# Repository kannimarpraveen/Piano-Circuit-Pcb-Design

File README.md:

# Piano Circuit PCB Design

## Description
Designed a piano circuit PCB using EAGLE, converting a schematic into a fully routed PCB layout ready for fabrication.

## Features
- Multi-key input circuit design
- Compact PCB layout with optimized routing
- Proper component placement and trace design
- Gerber file generation for manufacturing

## Tools Used
- Autodesk EAGLE

## Files Included
- Schematic design
- PCB layout

## Working
The circuit generates different tones based on key inputs, simulating a basic electronic piano functionality.

## Outcome
Developed practical experience in PCB design workflow from schematic creation to fabrication-ready output.

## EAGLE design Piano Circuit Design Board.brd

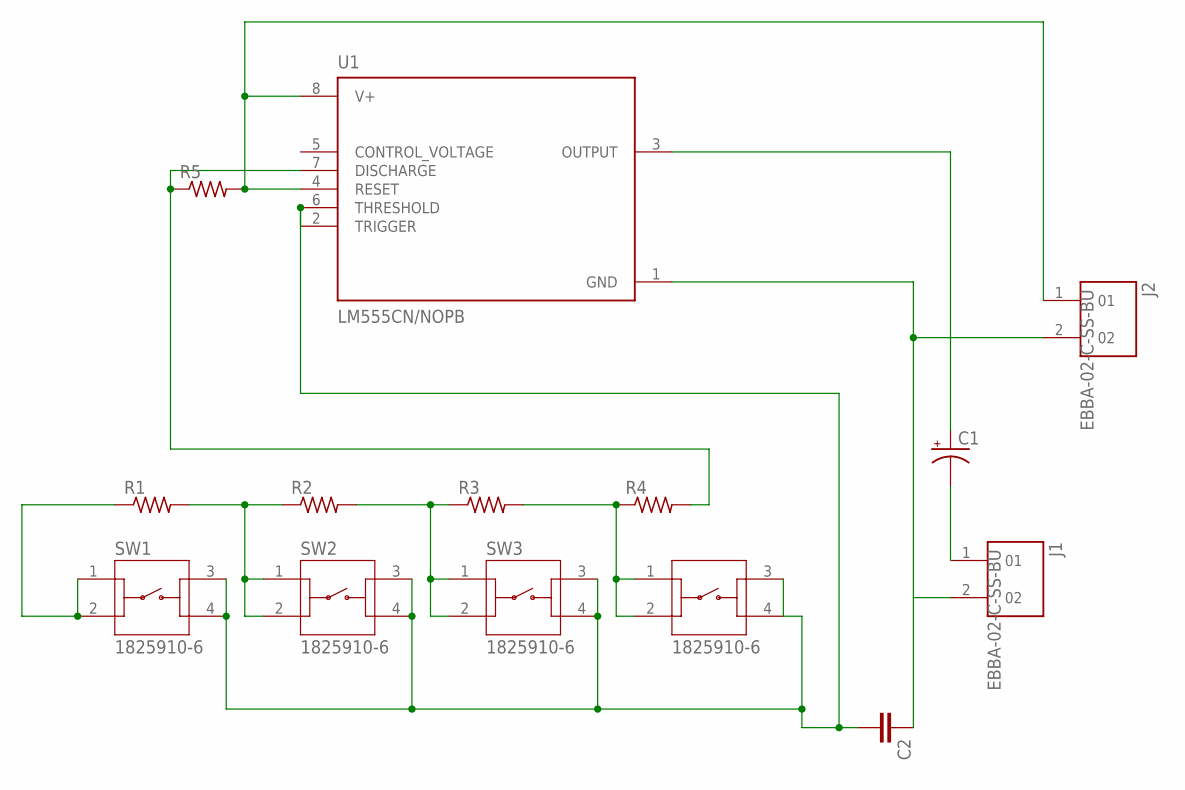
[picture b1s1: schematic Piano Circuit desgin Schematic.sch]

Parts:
C1: CPOL-USE2-4; E2-4
C2: C-EU025-025X050; C025-025X050
J1, J2: EBBA-02-C-SS-BU
R1, R2, R3, R4, R5: R-US_0204/7; 0204/7
SW1, SW2, SW3, SW4: 1825910-6; SW_1825910-6-4
U1: LM555CN/NOPB; DIP794W45P254L959H508Q8

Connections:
unnamed: R1.2, R2.1, SW2.1, SW2.2
unnamed: R2.2, R3.1, SW3.1, SW3.2
unnamed: R3.2, R4.1, SW4.1, SW4.2
unnamed: R1.1, SW1.1, SW1.2
unnamed: C2.1, J1.2, J2.2, U1.1 (GND)
unnamed: C1.+, U1.3 (OUTPUT)
unnamed: C1.-, J1.1
unnamed: J2.1, R5.2, U1.4 (RESET), U1.8 (V+)
unnamed: C2.2, SW1.3, SW1.4, SW2.3, SW2.4, SW3.3, SW3.4, SW4.3, SW4.4, U1.2 (TRIGGER), U1.6 (THRESHOLD)
unnamed: R4.2, R5.1, U1.7 (DISCHARGE)

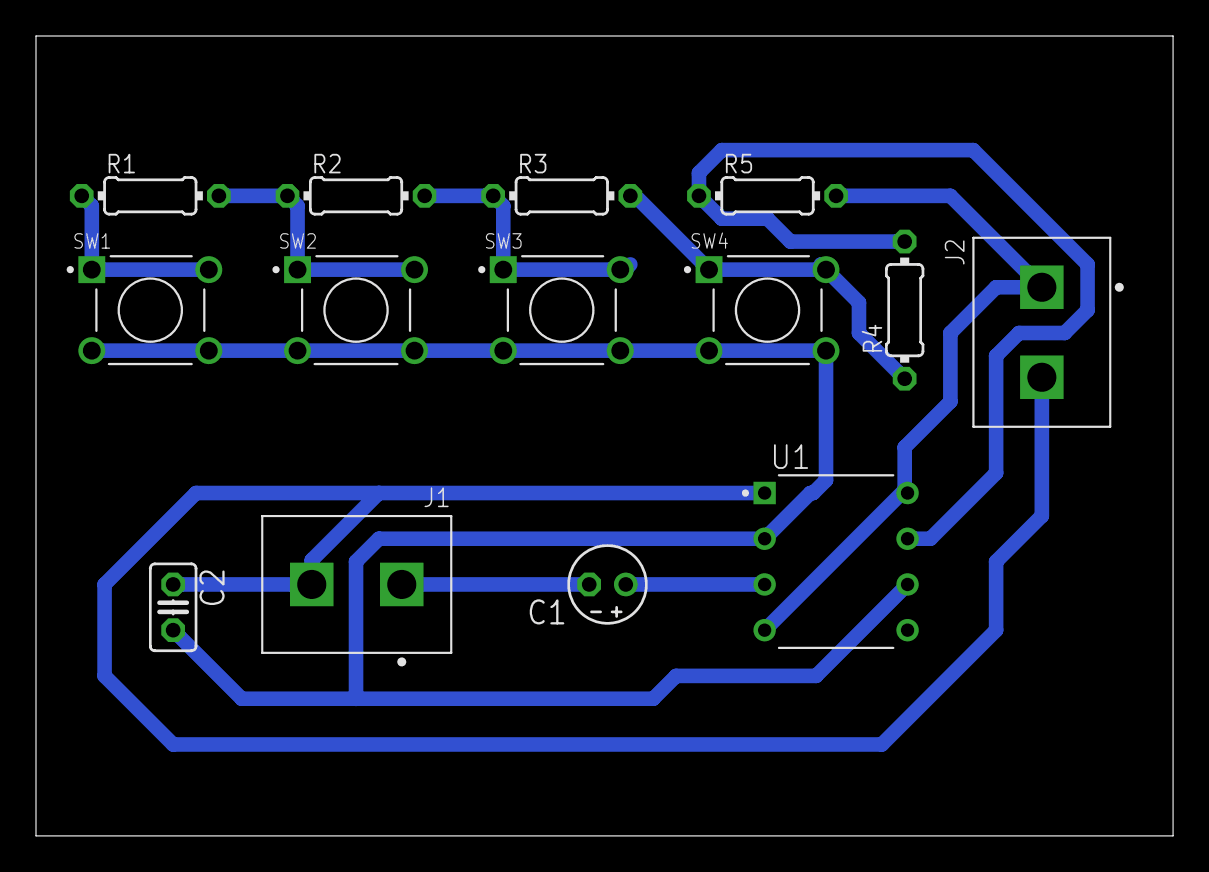
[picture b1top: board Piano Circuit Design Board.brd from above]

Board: 2 copper layers, 63.2 x 44.4 mm, 14 parts (0 on the bottom side), 10 nets.

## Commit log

2026-04-29 README.md
2026-04-29 Schematic and board files
    Recommended to Open with Eagle software only...
2026-04-29 Piano Circuit in Images (.jpeg) for reference
